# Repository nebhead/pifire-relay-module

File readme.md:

# PiFire Mechanical Relay Module PCB (v1.0.2) KiCad Files

## What is this? 

This PCB is designed to support mechanical relays for controlling incoming Power(L) to the Igniter, Auger, and AC Fan.  This board uses compact mechanical relays that are able to handle high power. This is an alternative to using an off the shelf relay module which simplifies the wiring and even allows you to use the OEM harness.  

The design intent for this board was to make a DIY accessible PCB that can be more easily put together by the maker/enthusiast of almost any skill level.  Full size components are used in most cases and most (if not all) parts should be readily available to order online.  See the [Interactive BOM](#interactive-bom) for more details about the parts used and links to order.

### What is PiFire? 

PiFire is a SBC based Pellet Smoker Controller.  More details can be found [here](https://nebhead.github.io/PiFire) or [at the GitHub repo](https://github.com/nebhead/pifire). 

## What's in this Repository?

### KiCad Project Files 
In this repository you will find the latest KiCad design files for the  PCB.  Simply load the project file (.kicad_pro) into the KiCad software and you should be able to edit as needed.  Or if you just want to get this board made, jump to the production section below.

### Interactive BOM

There is an interactive BOM located in the [/bom](bom/) folder which details the parts and provides some pin information as well.  Use this to gather the components you may need to build this board out and refer back to it for placement help.    

[BOM + Pin Info](https://nebhead.github.io/pifire-relay-module)

_This is a standalone HTML file that was autogenerated by the excellent plugin for KiCad. See the plugin here: [https://github.com/openscopeproject/InteractiveHtmlBom](https://github.com/openscopeproject/InteractiveHtmlBom)_

### PDF of the Schematic

Preview the schematic in PDF format here: [Schematic](schematic.pdf)

### JLCPCB Production Files

If you wish to get these PCBs made by JLCPCB, the production files are provided in the `/production` folder.  For convenience, the file `production.zip` can simply be uploaded to JLCPCB to make it super easy to order boards.

Drop the zip file onto the order page, wait for it to upload then simply continue to order the board.  Optionally, select different board color, PCB quantity, surface finish, etc.  Most of the default settings should be sufficient. 

### Links to the PCBs in this family of PiFire Boards

This PCB is part of a family of PCBs that can be used together to create  a full PiFire system.  Generally speaking you need the Main Module/Board, a Relay Control Board and a Probe Device board to have a basic PiFire system.  

**Main Module/Board** (required)
* [Main Board v4.0.x](https://github.com/nebhead/pifire-main-module-nopwr)

**Relay/Fan Control Boards** (choose one)
* [Mechanical Relay Module](https://github.com/nebhead/pifire-relay-module)
* [Solid State Relay Module](https://github.com/nebhead/pifire-relay-module-SSR)
* [Solid State Relay + PWM Fan Module](https://github.com/nebhead/pifire-relay-pwm-module-ssr) - Original Design
* [Solid State Relay + PWM Fan Module Alternate](https://github.com/nebhead/pifire-relay-pwm-module-ssr-alt) - Updated Design (Designed with help from @labmonkeyrat on Discord)

**Probe Device Board** (optional)
* [ADS Board](https://github.com/nebhead/pifire-ads-board) 

### 3D Printable Enclosures/Boxes 

With all of the 3D Prints for PiFire, a higher temperature filament such as PETG should be used.  PLA generally won't stand up to the temperatures that the components may be exposed to outdoors and near a hot smoker.  

#### Enclosure

Included here is an initial revision of the enclosure for this PCB.  The current models should be considered still in development and may have alignment challenges, etc. 

Except for the mounting wings, the majority of bolts to be used with this enclosure are M3. 

* STL: [Base](/printables/PiFire-v4-Relay-Base.stl)
* STL: [Lid](/printables/PiFire-v4-Relay-Lid.stl)
* OnShape: [Enclosure Original Models](https://cad.onshape.com/documents/03559f76f7adf190bf6f1259/w/7529cb0e4cd69db1a6a15202/e/07d5f9d46dc8f2b9e7dd655f?renderMode=0&uiState=66e11de950d7684b88999a0f)

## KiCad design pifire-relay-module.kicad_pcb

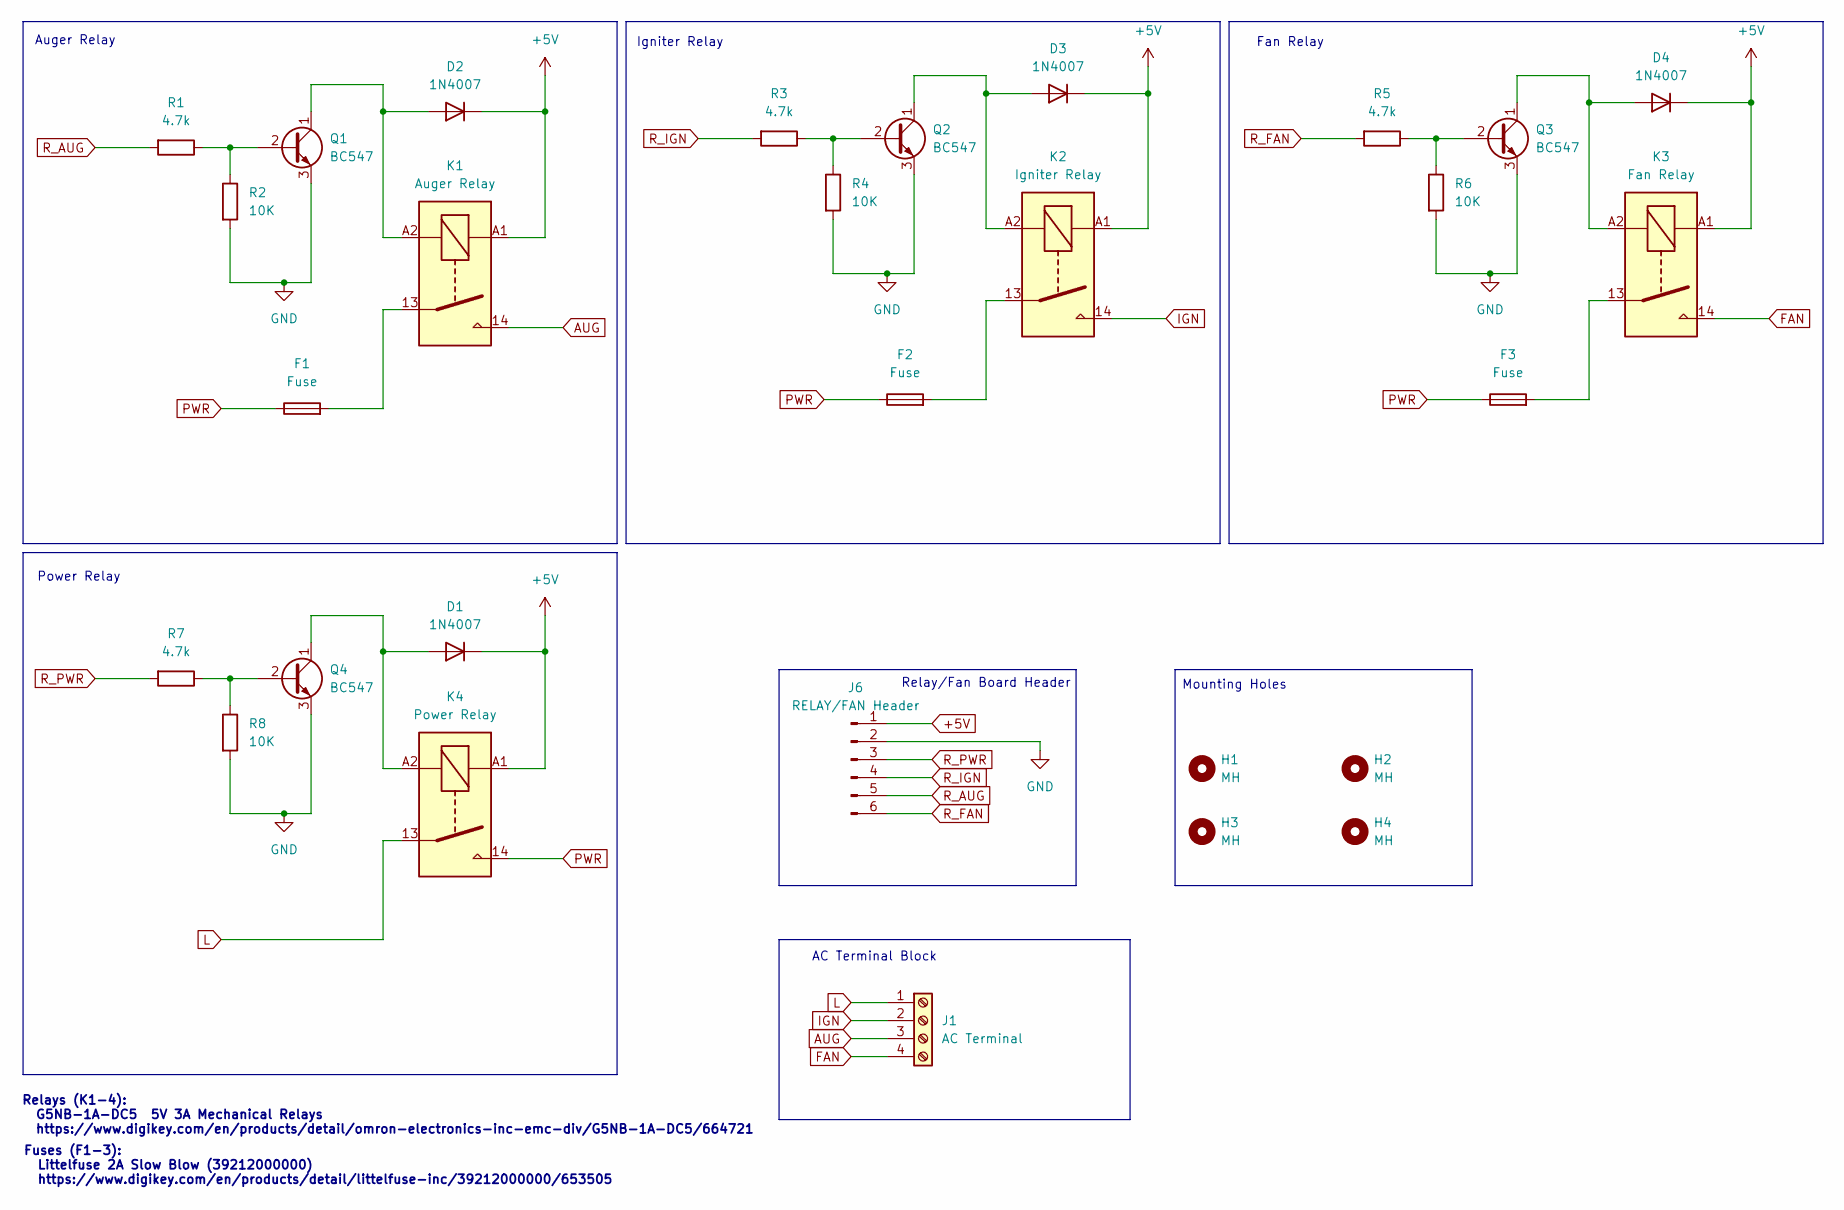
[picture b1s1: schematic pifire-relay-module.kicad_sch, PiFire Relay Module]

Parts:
D1, D2, D3, D4: 1N4007; D_DO-41_SOD81_P10.16mm_Horizontal
F1, F2, F3: Fuse; Fuse_Littelfuse_395Series
H1, H2, H3, H4: MH; MountingHole_3.2mm_M3
J1: AC Terminal; TerminalBlock_bornier-4_P5.08mm
J6: RELAY/FAN Header; JST_XH_B6B-XH-A_1x06_P2.50mm_Vertical
K1: Auger Relay; Relay_SPST_Omron_G5NB
K2: Igniter Relay; Relay_SPST_Omron_G5NB
K3: Fan Relay; Relay_SPST_Omron_G5NB
K4: Power Relay; Relay_SPST_Omron_G5NB
Q1, Q2, Q3, Q4: BC547; TO-92L_Inline
R1, R3, R5, R7: 4.7k; R_Axial_DIN0207_L6.3mm_D2.5mm_P7.62mm_Horizontal
R2, R4, R6, R8: 10K; R_Axial_DIN0207_L6.3mm_D2.5mm_P7.62mm_Horizontal

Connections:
+5V: D1.1 (K), D2.1 (K), D3.1 (K), D4.1 (K), J6.1, K1.A1, K2.A1, K3.A1, K4.A1
AUG: J1.3, K1.14
FAN: J1.4, K3.14
GND: J6.2, Q1.3 (E), Q2.3 (E), Q3.3 (E), Q4.3 (E), R2.2, R4.2, R6.2, R8.2
IGN: J1.2, K2.14
L: J1.1, K4.13
unnamed: D1.2 (A), K4.A2, Q4.1 (C)
unnamed: D2.2 (A), K1.A2, Q1.1 (C)
unnamed: D3.2 (A), K2.A2, Q2.1 (C)
unnamed: D4.2 (A), K3.A2, Q3.1 (C)
unnamed: F1.2, K1.13
unnamed: F2.2, K2.13
unnamed: F3.2, K3.13
unnamed: Q1.2 (B), R1.1, R2.1
unnamed: Q2.2 (B), R3.1, R4.1
unnamed: Q3.2 (B), R5.1, R6.1
unnamed: Q4.2 (B), R7.1, R8.1
PWR: F1.1, F2.1, F3.1, K4.14
R_AUG: J6.5, R1.2
R_FAN: J6.6, R5.2
R_IGN: J6.4, R3.2
R_PWR: J6.3, R7.2

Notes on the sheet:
Fan Relay
Power Relay
AC Terminal Block
Fuses (F1-3): Littelfuse 2A Slow Blow (39212000000) https://www.digikey.com/en/products/detail/littelfuse-inc/39212000000/653505
Auger Relay
Relay/Fan Board Header
Relays (K1-4): G5NB-1A-DC5 5V 3A Mechanical Relays https://www.digikey.com/en/products/detail/omron-electronics-inc-emc-div/G5NB-1A-DC5/664721
Mounting Holes
Igniter Relay

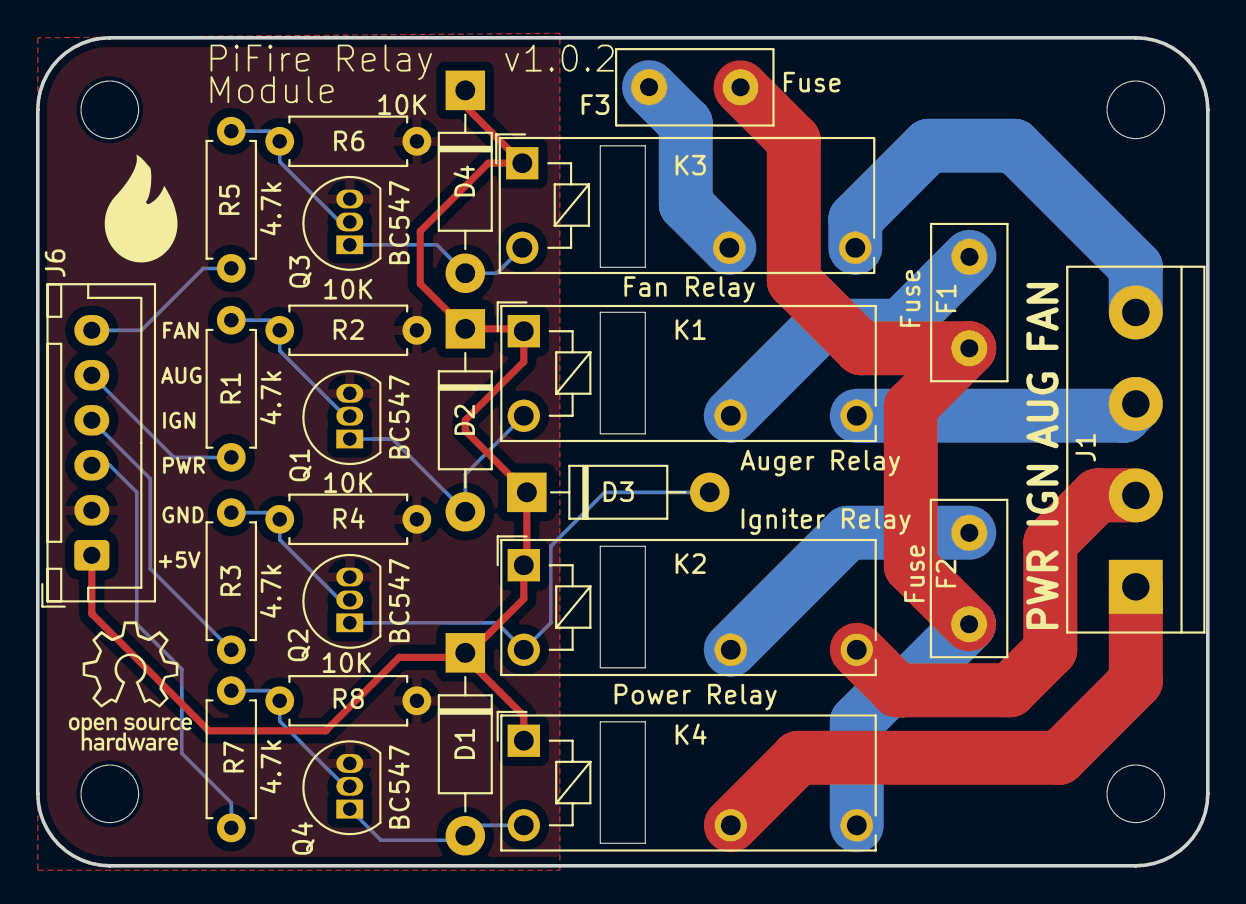
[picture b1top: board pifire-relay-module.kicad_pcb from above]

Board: 2 copper layers, 65.0 x 46.0 mm, 29 parts (0 on the bottom side), 22 nets.

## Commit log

2024-05-10 Adding license.txt
2024-05-10 Modify gitignore
2024-09-07 Update readme.md
    Update links to the PWM boards.
2024-09-11 Auto stash before merge of "main" and "origin/main"
